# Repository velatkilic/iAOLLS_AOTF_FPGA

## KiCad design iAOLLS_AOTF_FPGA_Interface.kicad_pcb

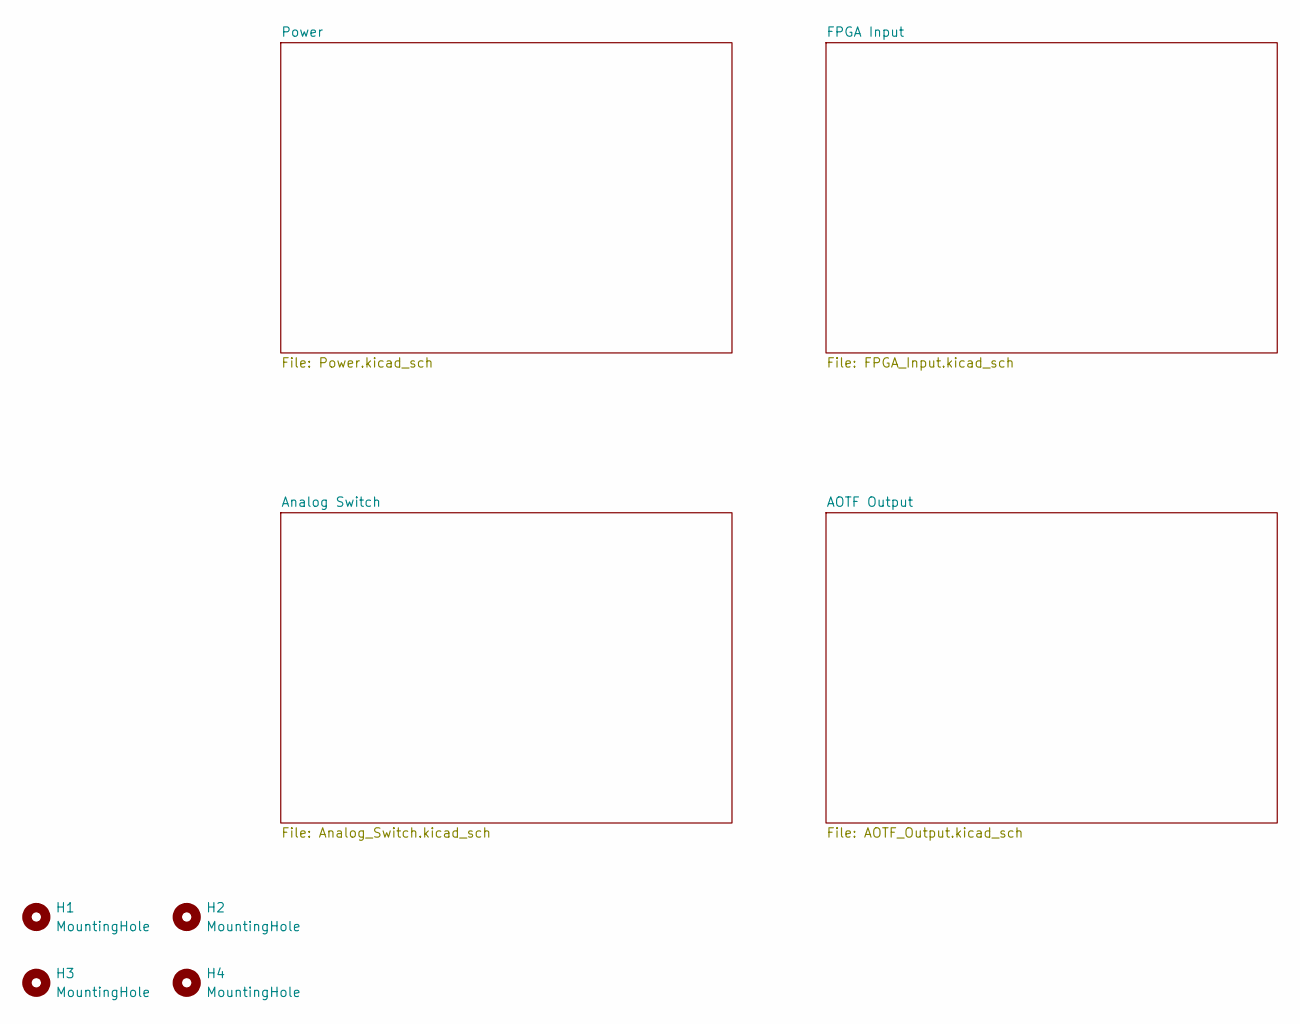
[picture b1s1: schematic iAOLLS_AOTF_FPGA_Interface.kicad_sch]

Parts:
H1, H2, H3, H4: MountingHole; MountingHole_3.2mm_M3_Pad_Via

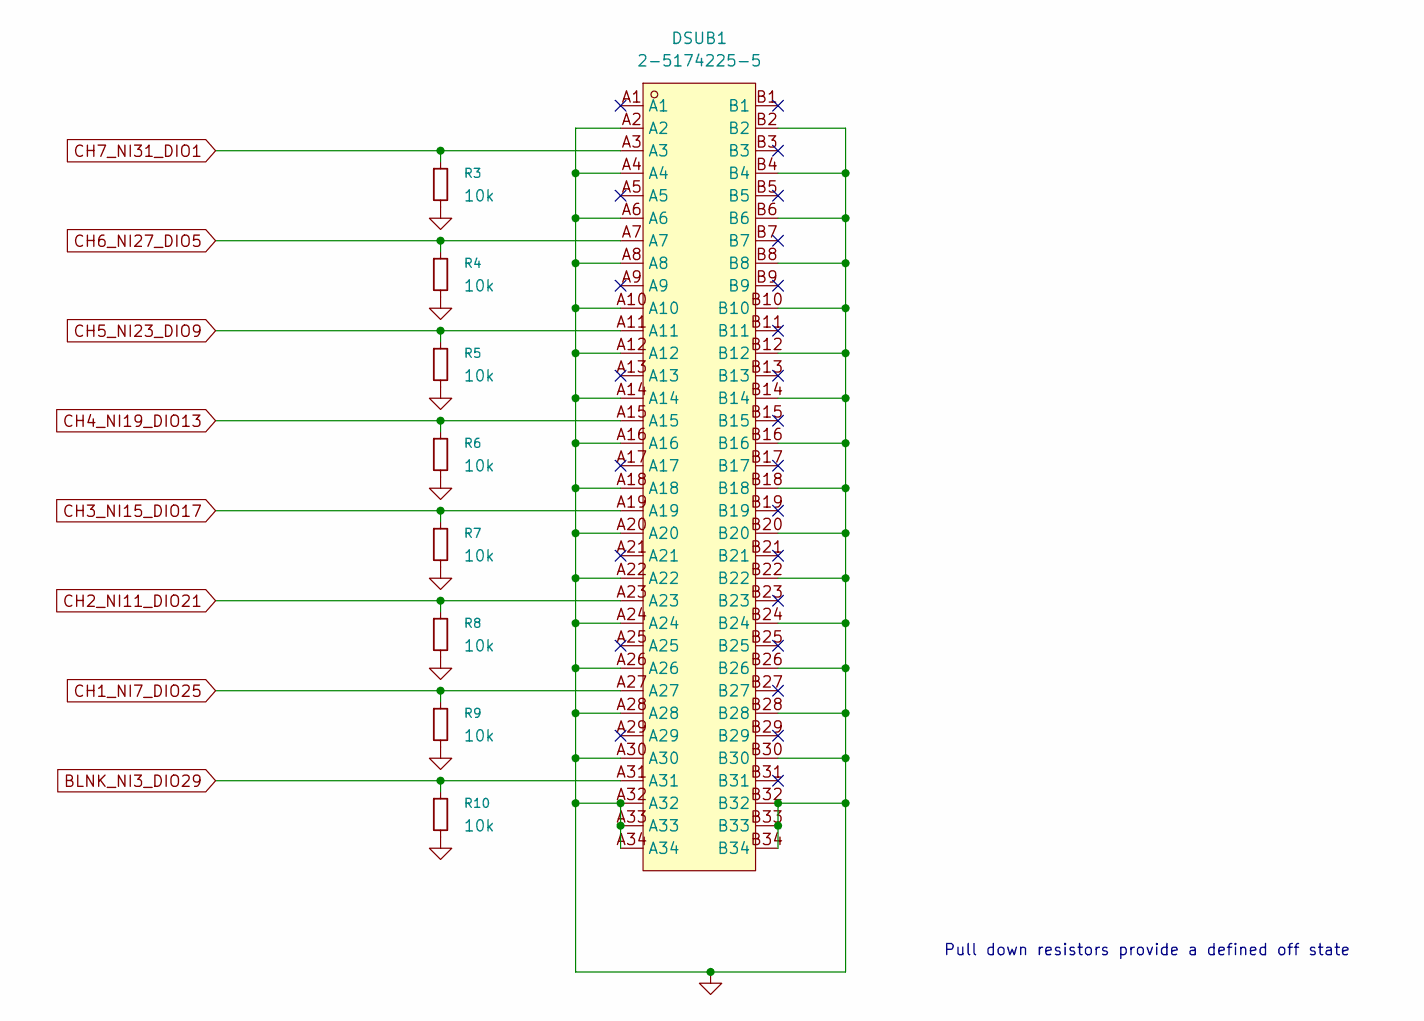
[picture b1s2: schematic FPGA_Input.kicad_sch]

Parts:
DSUB1: 2-5174225-5; DSUB-TH_68P_2-5174225-5; MPN 2-5174225-5; LCSC Part C3134184
R3, R4, R5, R6, R7, R8, R9, R10: 10k; R_0603_1608Metric

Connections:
BLNK_NI3_DIO29: DSUB1.A31, R10.1; also elsewhere on the board
CH1_NI7_DIO25: DSUB1.A27, R9.1; also elsewhere on the board
CH2_NI11_DIO21: DSUB1.A23, R8.1; also elsewhere on the board
CH3_NI15_DIO17: DSUB1.A19, R7.1; also elsewhere on the board
CH4_NI19_DIO13: DSUB1.A15, R6.1; also elsewhere on the board
CH5_NI23_DIO9: DSUB1.A11, R5.1; also elsewhere on the board
CH6_NI27_DIO5: DSUB1.A7, R4.1; also elsewhere on the board
CH7_NI31_DIO1: DSUB1.A3, R3.1; also elsewhere on the board
GND: DSUB1.A2, DSUB1.A4, DSUB1.A6, DSUB1.A8, DSUB1.A10, DSUB1.A12, DSUB1.A14, DSUB1.A16, DSUB1.A18, DSUB1.A20, DSUB1.A22, DSUB1.A24, DSUB1.A26, DSUB1.A28, DSUB1.A30, DSUB1.A32, DSUB1.A33, DSUB1.A34, DSUB1.B2, DSUB1.B4, DSUB1.B6, DSUB1.B8, DSUB1.B10, DSUB1.B12, DSUB1.B14, DSUB1.B16, DSUB1.B18, DSUB1.B20, DSUB1.B22, DSUB1.B24, DSUB1.B26, DSUB1.B28, DSUB1.B30, DSUB1.B32, DSUB1.B33, DSUB1.B34, R3.2, R4.2, R5.2, R6.2, R7.2, R8.2, R9.2, R10.2; also elsewhere on the board

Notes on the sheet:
Pull down resistors provide a defined off state

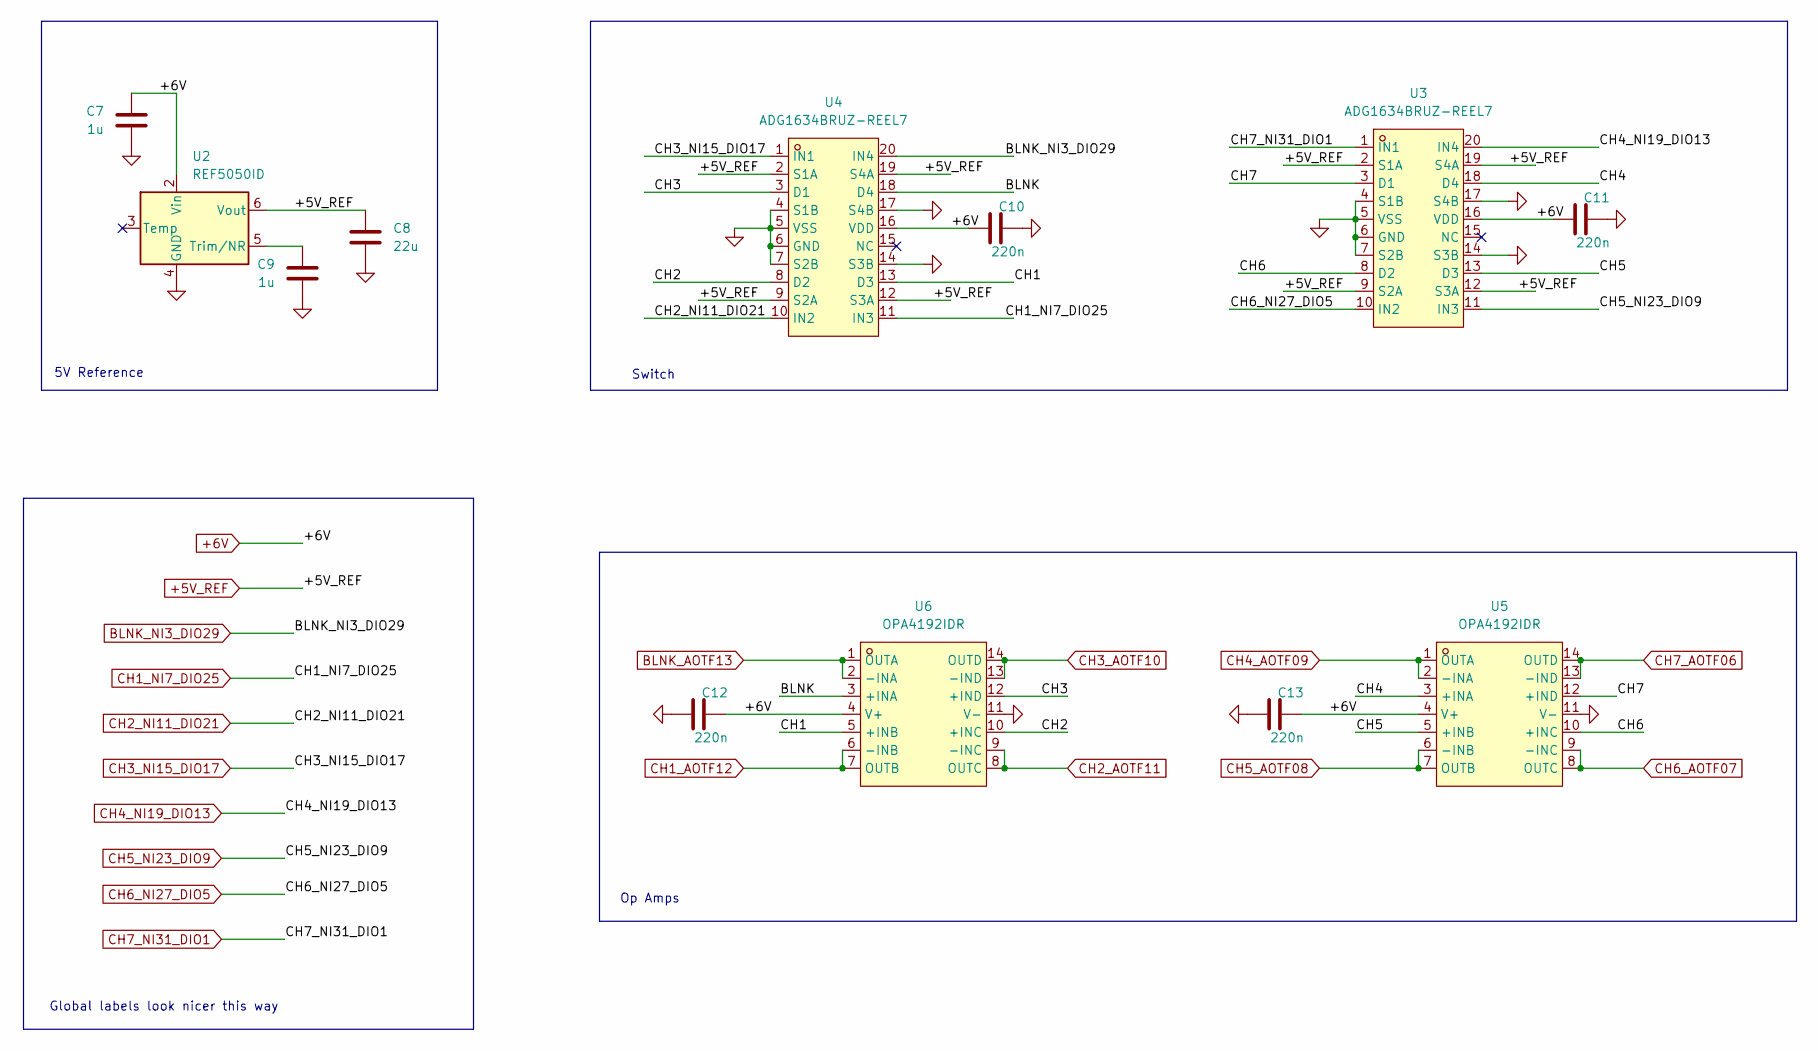
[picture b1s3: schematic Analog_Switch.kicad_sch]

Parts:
C7, C9: 1u; C_0603_1608Metric
C8: 22u; C_1206_3216Metric
C10, C11, C12, C13: 220n; C_0805_2012Metric
U2: REF5050ID; SOIC-8_3.9x4.9mm_P1.27mm
U3, U4: ADG1634BRUZ-REEL7; TSSOP-20_L6.5-W4.4-P0.65-LS6.4-BL; MPN ADG1634BRUZ-REEL7; LCSC Part C579038
U5, U6: OPA4192IDR; SOIC-14_L8.7-W3.9-P1.27-LS6.0-BL; MPN OPA4192IDR; LCSC Part C2057908

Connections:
+5V_REF: C8.1, U2.6 (Vout), U3.2 (S1A), U3.9 (S2A), U3.12 (S3A), U3.19 (S4A), U4.2 (S1A), U4.9 (S2A), U4.12 (S3A), U4.19 (S4A)
+6V: C7.1, C10.1, C11.1, C12.2, C13.2, U2.2 (Vin), U3.16 (VDD), U4.16 (VDD), U5.4 (V+), U6.4 (V+); also elsewhere on the board
/Analog Switch/BLNK: U4.18 (D4), U6.3 (+INA)
/Analog Switch/CH1: U4.13 (D3), U6.5 (+INB)
/Analog Switch/CH2: U4.8 (D2), U6.10 (+INC)
/Analog Switch/CH3: U4.3 (D1), U6.12 (+IND)
/Analog Switch/CH4: U3.18 (D4), U5.3 (+INA)
/Analog Switch/CH5: U3.13 (D3), U5.5 (+INB)
/Analog Switch/CH6: U3.8 (D2), U5.10 (+INC)
/Analog Switch/CH7: U3.3 (D1), U5.12 (+IND)
BLNK_AOTF13: U6.1 (OUTA), U6.2 (-INA); also elsewhere on the board
BLNK_NI3_DIO29: U4.20 (IN4); also elsewhere on the board
CH1_AOTF12: U6.6 (-INB), U6.7 (OUTB); also elsewhere on the board
CH1_NI7_DIO25: U4.11 (IN3); also elsewhere on the board
CH2_AOTF11: U6.8 (OUTC), U6.9 (-INC); also elsewhere on the board
CH2_NI11_DIO21: U4.10 (IN2); also elsewhere on the board
CH3_AOTF10: U6.13 (-IND), U6.14 (OUTD); also elsewhere on the board
CH3_NI15_DIO17: U4.1 (IN1); also elsewhere on the board
CH4_AOTF09: U5.1 (OUTA), U5.2 (-INA); also elsewhere on the board
CH4_NI19_DIO13: U3.20 (IN4); also elsewhere on the board
CH5_AOTF08: U5.6 (-INB), U5.7 (OUTB); also elsewhere on the board
CH5_NI23_DIO9: U3.11 (IN3); also elsewhere on the board
CH6_AOTF07: U5.8 (OUTC), U5.9 (-INC); also elsewhere on the board
CH6_NI27_DIO5: U3.10 (IN2); also elsewhere on the board
CH7_AOTF06: U5.13 (-IND), U5.14 (OUTD); also elsewhere on the board
CH7_NI31_DIO1: U3.1 (IN1); also elsewhere on the board
GND: C7.2, C8.2, C9.2, C10.2, C11.2, C12.1, C13.1, U2.4 (GND), U3.4 (S1B), U3.5 (VSS), U3.6 (GND), U3.7 (S2B), U3.14 (S3B), U3.17 (S4B), U4.4 (S1B), U4.5 (VSS), U4.6 (GND), U4.7 (S2B), U4.14 (S3B), U4.17 (S4B), U5.11 (V-), U6.11 (V-); also elsewhere on the board
unnamed: C9.1, U2.5 (Trim/NR)

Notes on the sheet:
Op Amps
Switch
Global labels look nicer this way
5V Reference

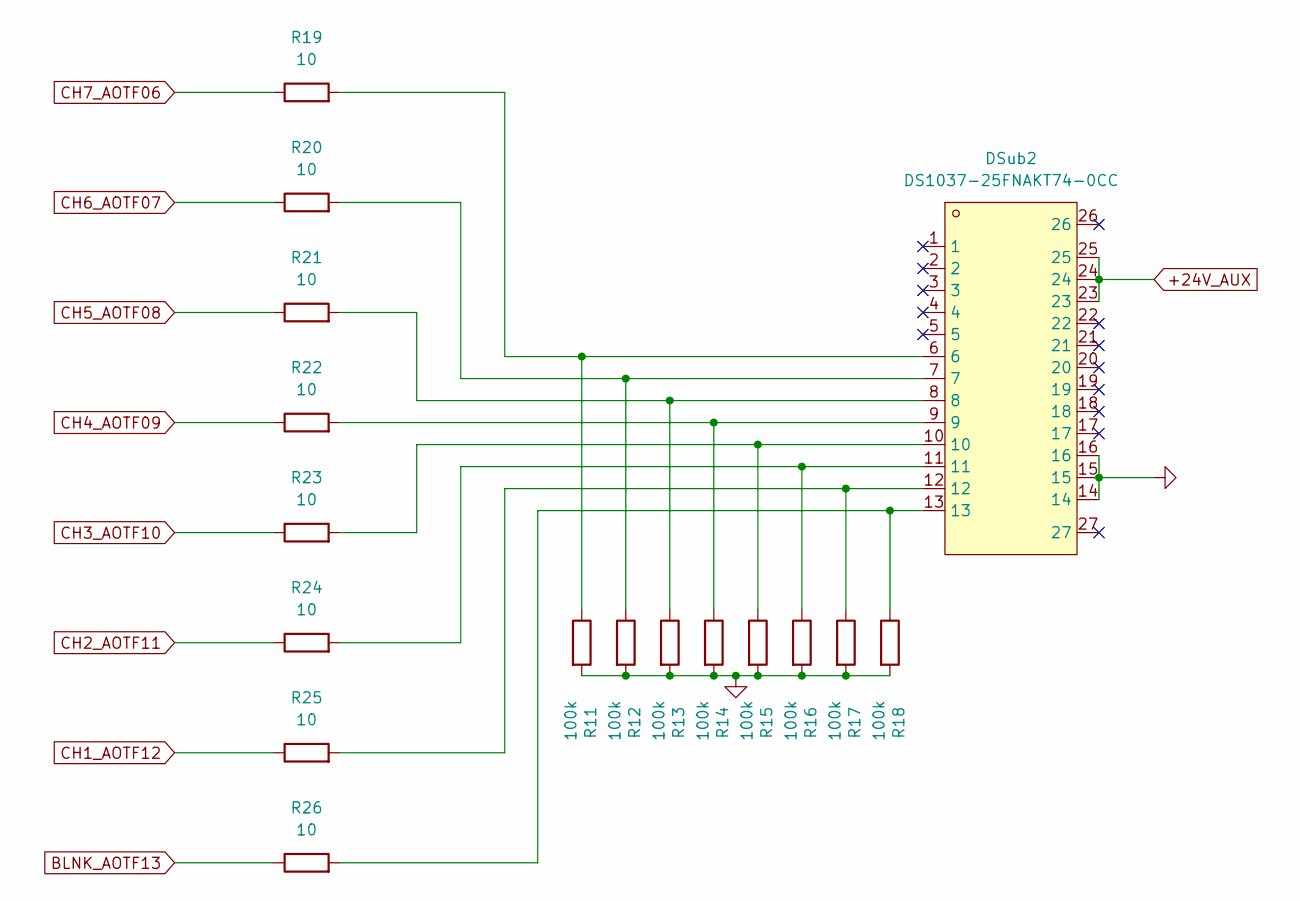
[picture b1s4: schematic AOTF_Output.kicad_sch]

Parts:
DSub2: DS1037-25FNAKT74-0CC; DSUB-TH_DS1037-25FNAKT74-0CC; MPN DS1037-25FNAKT74-0CC; LCSC Part C77838
R11, R12, R13, R14, R15, R16, R17, R18: 100k; R_0603_1608Metric
R19, R20, R21, R22, R23, R24, R25, R26: 10; R_0603_1608Metric

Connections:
+24V_AUX: DSub2.23, DSub2.24, DSub2.25; also elsewhere on the board
BLNK_AOTF13: R26.1; also elsewhere on the board
CH1_AOTF12: R25.1; also elsewhere on the board
CH2_AOTF11: R24.1; also elsewhere on the board
CH3_AOTF10: R23.1; also elsewhere on the board
CH4_AOTF09: R22.1; also elsewhere on the board
CH5_AOTF08: R21.1; also elsewhere on the board
CH6_AOTF07: R20.1; also elsewhere on the board
CH7_AOTF06: R19.1; also elsewhere on the board
GND: DSub2.14, DSub2.15, DSub2.16, R11.2, R12.2, R13.2, R14.2, R15.2, R16.2, R17.2, R18.2; also elsewhere on the board
unnamed: DSub2.6, R11.1, R19.2
unnamed: DSub2.7, R12.1, R20.2
unnamed: DSub2.8, R13.1, R21.2
unnamed: DSub2.9, R14.1, R22.2
unnamed: DSub2.10, R15.1, R23.2
unnamed: DSub2.11, R16.1, R24.2
unnamed: DSub2.12, R17.1, R25.2
unnamed: DSub2.13, R18.1, R26.2

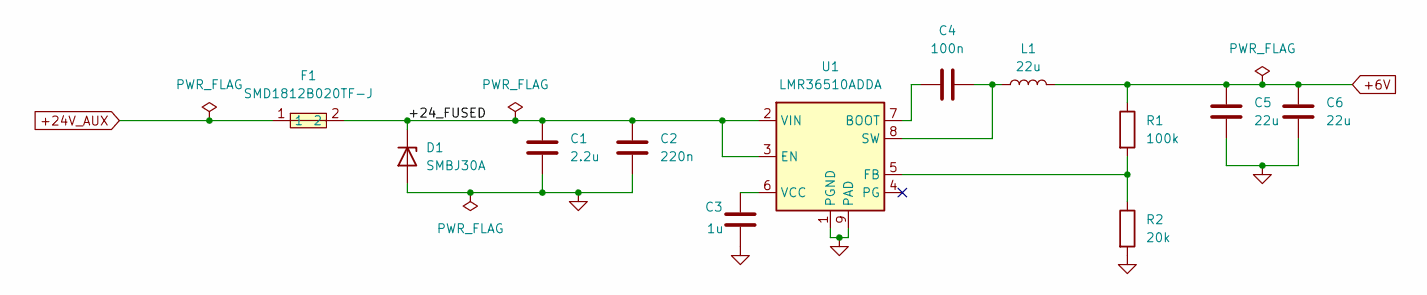
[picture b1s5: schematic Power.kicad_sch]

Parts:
C1: 2.2u; C_1210_3225Metric
C2: 220n; C_0805_2012Metric
C3: 1u; C_0603_1608Metric
C4: 100n; C_0603_1608Metric
C5, C6: 22u; C_1206_3216Metric
D1: SMBJ30A; D_SMB
F1: SMD1812B020TF-J; R1812; MPN SMD1812B020TF-J; LCSC Part C269125
L1: 22u; IND-SMD_L7.8-W7.0_FXC0630
R1: 100k; R_0603_1608Metric
R2: 20k; R_0603_1608Metric
U1: LMR36510ADDA; Texas_HTSOP-8-1EP_3.9x4.9mm_P1.27mm_EP2.95x4.9mm_Mask2.4x3.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

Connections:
+6V: C5.1, C6.1, L1.2, R1.1; also elsewhere on the board
+24V_AUX: F1.1; also elsewhere on the board
/Power/+24_FUSED: C1.1, C2.1, D1.1 (K), F1.2, U1.2 (VIN), U1.3 (EN)
GND: C1.2, C2.2, C3.2, C5.2, C6.2, D1.2 (A), R2.2, U1.1 (PGND), U1.9 (PAD); also elsewhere on the board
unnamed: C4.1, U1.7 (BOOT)
unnamed: R1.2, R2.1, U1.5 (FB)
unnamed: C4.2, L1.1, U1.8 (SW)
unnamed: C3.1, U1.6 (VCC)

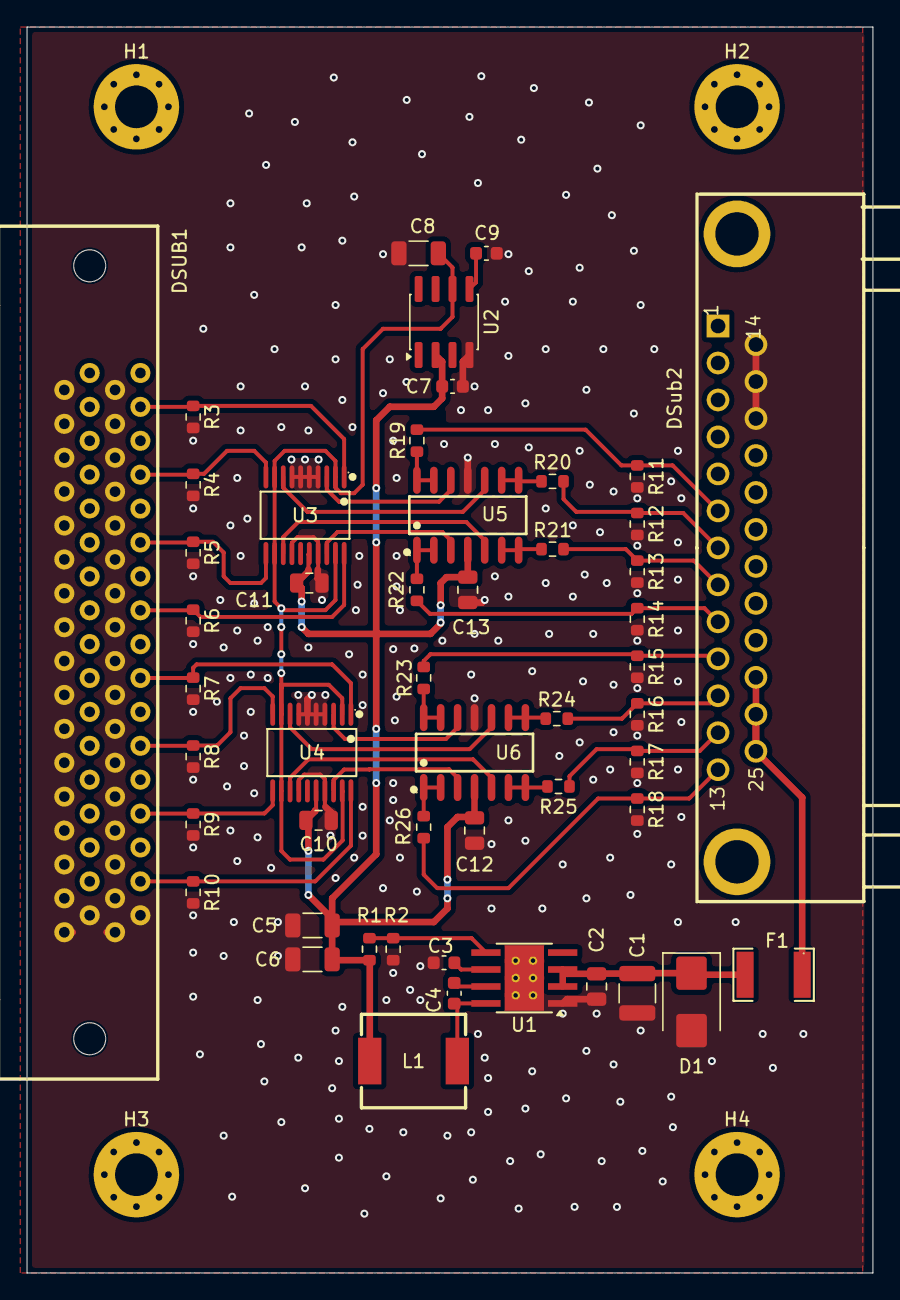
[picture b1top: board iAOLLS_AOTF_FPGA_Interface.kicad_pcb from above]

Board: 2 copper layers, 63.4 x 93.3 mm, 54 parts (0 on the bottom side), 42 nets.
